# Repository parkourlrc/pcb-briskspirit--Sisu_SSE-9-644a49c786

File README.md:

# Sisu SSE-9

Sisu SSE-9 is an experimental six-layer replacement mainboard for the Nokia
3210 mechanical platform. It keeps the original enclosure, keypad, display,
audio contacts, battery contacts, and bottom connector while replacing the
electronics with an RP2354B application controller and a Telit LE910C1-WWX LTE
module.

Rev B2 has been fabricated and hand assembled. The board is suitable for
development and bring-up, but it is not a drop-in production design.

> [!WARNING]
> Rev B2 has known hardware faults and required post-assembly rework. Read
> [ERRATA.md](ERRATA.md) before ordering, assembling, or powering a board.

| Front | Back |
| --- | --- |
|  |  |

## Key Features

- RP2354B microcontroller with local QSPI flash
- Telit LE910C1-WWX LTE modem and configurable antenna matching networks
- TCA8418 keypad scanner for the original dome-key matrix
- NAU88C22 audio codec with the original earpiece, microphone, speaker, and buzzer interfaces
- BQ25171 dual-chemistry charger support for NiMH and Li-ion development
- LTC2959 charge and current measurement
- RV-8803-C7 real-time clock
- Local symbols, footprints, and 3D models needed by the design
- Service/debug pogo adapter under `subassemblies/debug_pogo_adapter`

## Repository Layout

- `Sisu_SSE-9.kicad_pro`: main KiCad project
- `Sisu_SSE-9.kicad_pcb`: Rev B2 mainboard layout
- `*.kicad_sch`: root and hierarchical schematics
- `lib_10/`: project-local symbols, footprints, and 3D models
- `Sisu_SSE-9_bom_filled.xlsx`: grouped BOM with sourcing and review notes
- `Ordering/`: historical manufacturing archives for fabricated revisions
- `subassemblies/debug_pogo_adapter/`: pogo-to-JST service adapter
- `ERRATA.md`: known Rev B2 faults, rework, and validation limits

## Opening the Project

The current files are saved with KiCad 10.0.5. Clone the repository and open
`Sisu_SSE-9.kicad_pro` from KiCad's project manager. The symbol and footprint
tables use project-relative paths, so no shared user library is required.

```sh
git clone https://github.com/briskspirit/Sisu_SSE-9.git
cd Sisu_SSE-9
```

Older KiCad releases cannot read this project's file format reliably.

## BOM and Assembly

`Sisu_SSE-9.csv`, `Sisu_SSE-9_bom_filled.csv`, and
`Sisu_SSE-9_bom_filled.xlsx` are generated from the current post-assembly Rev
B2 source. The filled workbook retains supplier-review notes, but stock status
is only a historical snapshot and must be checked again before ordering.

RF tuning positions intentionally have no final MPN. Their values are
provisional and depend on the antenna, enclosure, assembly, and calibration.
Mechanical contact footprints such as the display zebra, speaker, motor, and
spring contacts remain visible in the engineering BOM but are excluded from
placement output.

## Manufacturing Archives

The ZIP files under `Ordering/` are immutable records of data sent for previous
fabrication runs. They are useful for comparison, not as the preferred source
for another order. The root KiCad files include post-assembly corrections that
are newer than the Rev B2 archive.

Before fabrication:

1. Read [ERRATA.md](ERRATA.md).
2. Run ERC and DRC with KiCad 10.0.5.
3. Re-export Gerbers, drill files, position files, and the BOM from the root project.
4. Review every fabrication output independently, especially RF footprints, plated holes, and DNP status.

## Current Status

- Rev A established the mechanical and electrical baseline.
- Rev B1 used the u-blox LARA-R6 modem.
- Rev B2 moved to the Telit LE910C1-WWX and is under hardware bring-up.
- Rev C is planned to address the published errata and power-management findings.

Firmware is developed in the sibling `Sisu_DCP-3` project and will be linked
here when its public repository is available.

## Contributing

Issue reports, measurements, footprint corrections, and tested design changes
are welcome. Please identify the board revision, modem variant, battery
chemistry, and the exact test conditions. Hardware changes should include ERC
and DRC results plus a review of generated fabrication data.

## License

Original project material is released under the [Unlicense](COPYING).
Third-party material remains the property of its respective owners; see
[THIRD_PARTY_NOTICES.md](THIRD_PARTY_NOTICES.md).

## Acknowledgements

- KiCad and its library contributors
- Raspberry Pi, Telit, Texas Instruments, Nuvoton, Micro Crystal, and the other component manufacturers whose documentation made this work possible
- The original Nokia 3210 engineering and industrial-design teams

Nokia is a trademark of Nokia Corporation. This is an independent hobby project
and is not affiliated with or endorsed by Nokia, HMD Global, Telit, Raspberry
Pi, or any component manufacturer.

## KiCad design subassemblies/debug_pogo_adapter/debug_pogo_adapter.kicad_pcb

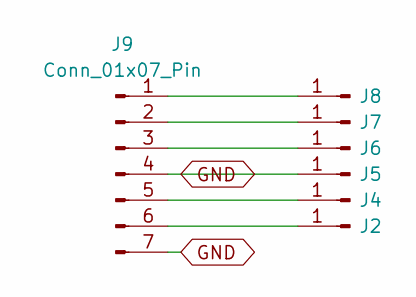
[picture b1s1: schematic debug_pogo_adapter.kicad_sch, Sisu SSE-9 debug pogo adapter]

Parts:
J2, J4, J5, J6, J7, J8: Conn_01x01_Pin; SAMESKY_CPG-01-TH-B
J9: Conn_01x07_Pin; JST_PH_B6B-PH-SM4-TB_1x06-1MP_P2.00mm_Vertical_Shell_GND

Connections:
GND: J5.1 (Pin_1_1), J9.4, J9.7
unnamed: J2.1 (Pin_1_1), J9.6
unnamed: J4.1 (Pin_1_1), J9.5
unnamed: J6.1 (Pin_1_1), J9.3
unnamed: J7.1 (Pin_1_1), J9.2
unnamed: J8.1 (Pin_1_1), J9.1

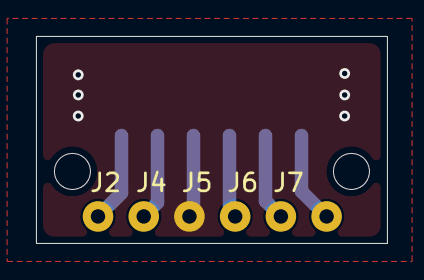
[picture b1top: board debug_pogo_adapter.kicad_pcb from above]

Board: 2 copper layers, 19.5 x 11.5 mm, 7 parts (1 on the bottom side), 6 nets.

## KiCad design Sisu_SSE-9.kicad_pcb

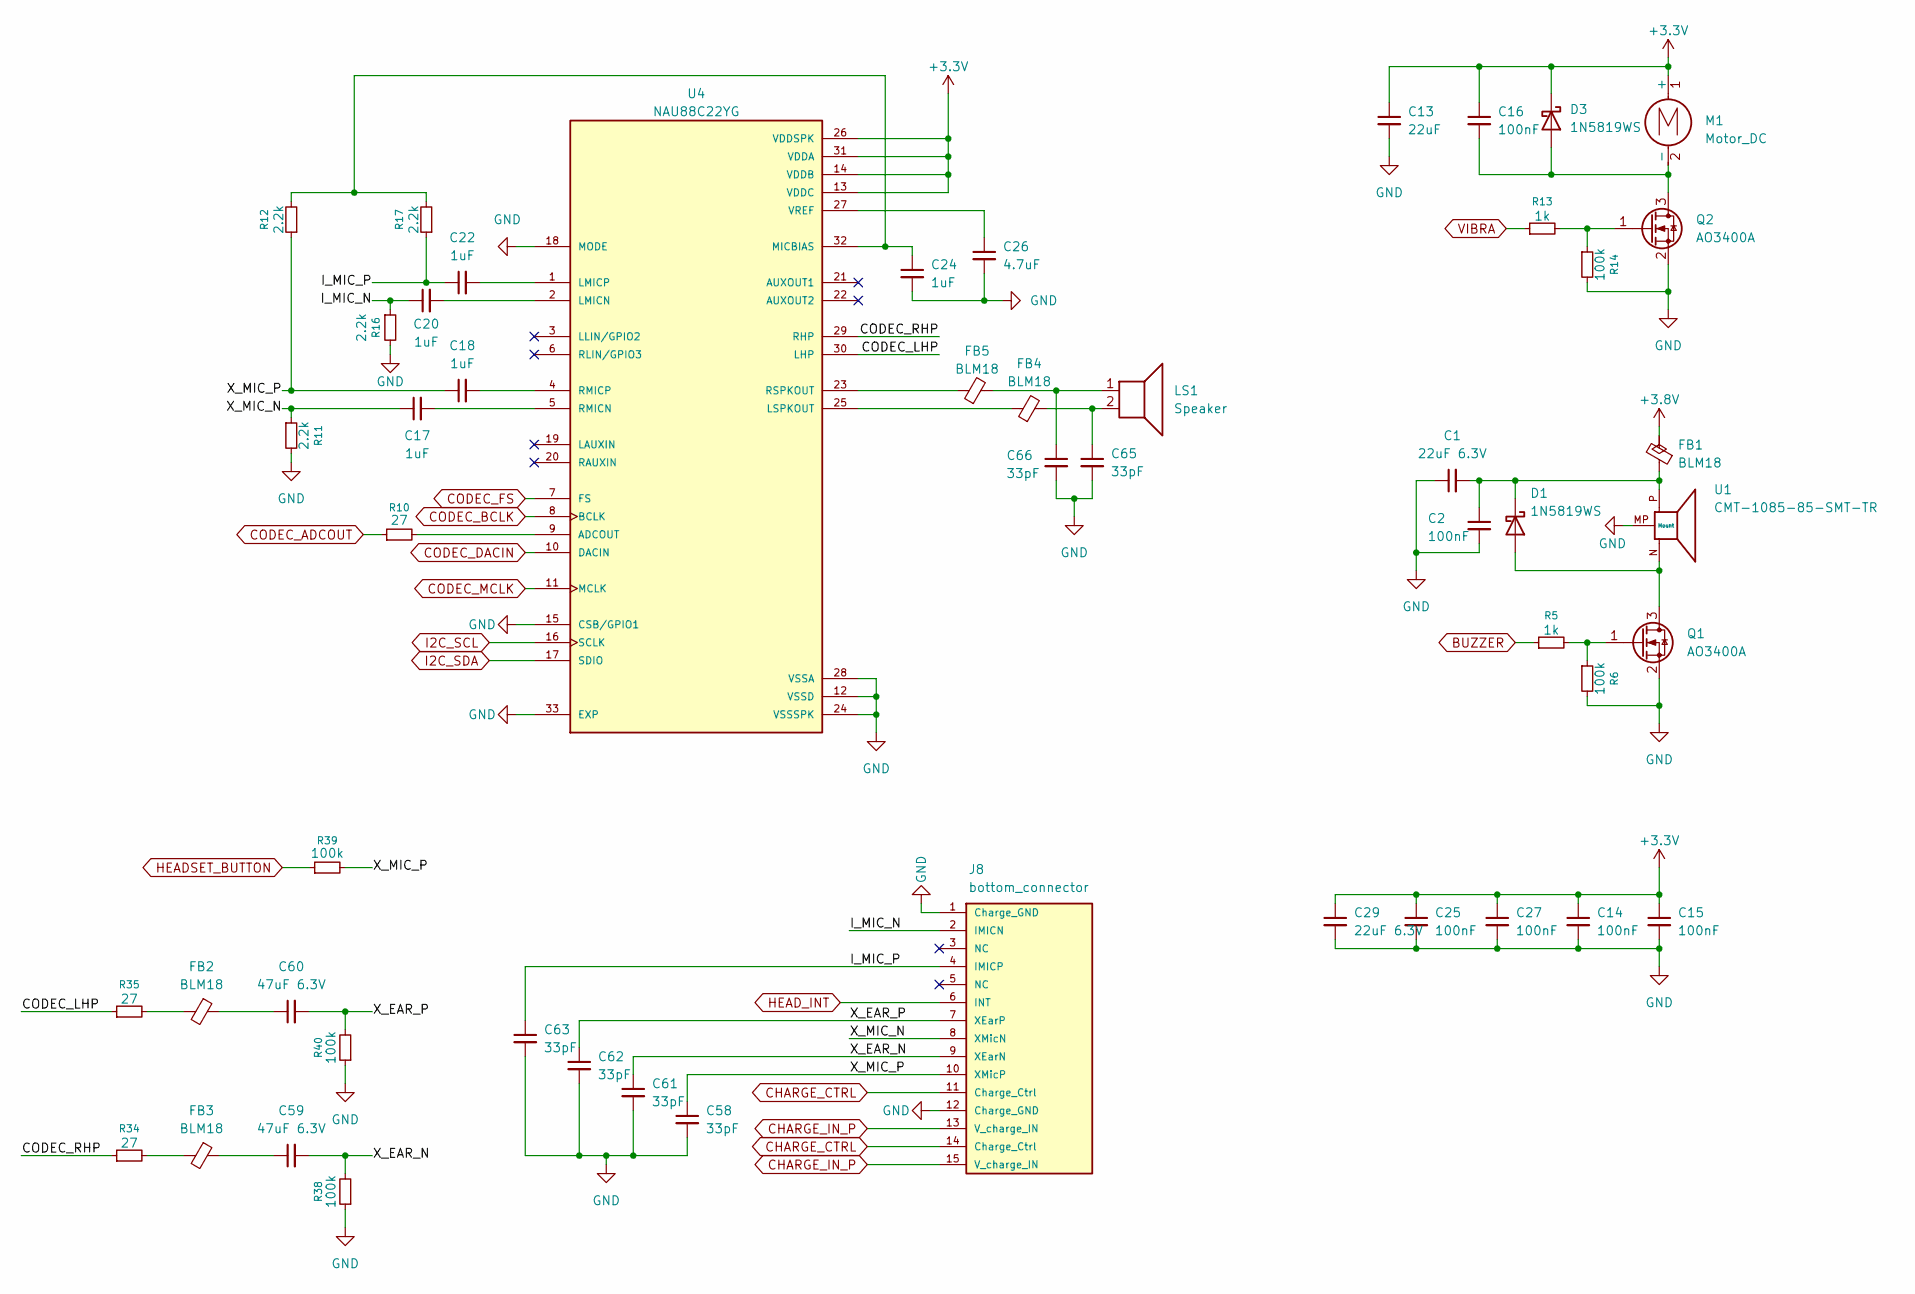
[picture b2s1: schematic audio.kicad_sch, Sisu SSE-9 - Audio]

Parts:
C1, C29: 22uF 6.3V; C_0603_1608Metric
C2, C14, C15, C16, C25, C27: 100nF; C_0402_1005Metric
C13: 22uF; C_0603_1608Metric
C17, C18, C20, C22, C24: 1uF; C_0402_1005Metric
C26: 4.7uF; C_0402_1005Metric
C58, C61, C62, C63, C65, C66: 33pF; C_0402_1005Metric
C59, C60: 47uF 6.3V; C_0805_2012Metric
D1, D3: 1N5819WS; D_SOD-323
FB1, FB2, FB3, FB4, FB5: BLM18; L_0603_1608Metric
J8: bottom_connector; 3210_bottom_conn
LS1: Speaker; Speaker_contact_pads
M1: Motor_DC; 3210_vibra_motor
Q1, Q2: AO3400A; SOT-23
R5, R13: 1k; R_0402_1005Metric
R6, R14, R38, R39, R40: 100k; R_0402_1005Metric
R10, R34, R35: 27; R_0402_1005Metric
R11, R12, R16, R17: 2.2k; R_0402_1005Metric
U1: CMT-1085-85-SMT-TR; MagneticBuzzer_CUI_CMT-1085-85-SMT-TR; PARTREV 1.01
U4: NAU88C22YG; QFN-32-1EP_5x5mm_P0.5mm_EP3.1x3.1mm; PARTREV 3.3

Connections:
+3.3V: C13.1, C14.1, C15.1, C16.1, C25.1, C27.1, C29.1, D3.1 (K), M1.1 (+), U4.13 (VDDC), U4.14 (VDDB), U4.26 (VDDSPK), U4.31 (VDDA); also elsewhere on the board
+3.8V: FB1.2; also elsewhere on the board
/AUDIO/CODEC_LHP: R35.1, U4.30 (LHP)
/AUDIO/CODEC_RHP: R34.1, U4.29 (RHP)
/AUDIO/I_MIC_N: C20.1, J8.2 (IMICN), R16.1
/AUDIO/I_MIC_P: C22.1, C63.1, J8.4 (IMICP), R17.1
/AUDIO/X_EAR_N: C59.2, C61.1, J8.9 (XEarN), R38.2
/AUDIO/X_EAR_P: C60.2, C62.1, J8.7 (XEarP), R40.2
/AUDIO/X_MIC_N: C17.1, J8.8 (XMicN), R11.1
/AUDIO/X_MIC_P: C18.1, C58.1, J8.10 (XMicP), R12.1, R39.2
BUZZER: R5.1; also elsewhere on the board
CHARGE_CTRL: J8.11 (Charge_Ctrl), J8.14 (Charge_Ctrl); also elsewhere on the board
CHARGE_IN_P: J8.13 (V_charge_IN), J8.15 (V_charge_IN); also elsewhere on the board
CODEC_ADCOUT: R10.1; also elsewhere on the board
CODEC_BCLK: U4.8 (BCLK); also elsewhere on the board
CODEC_DACIN: U4.10 (DACIN); also elsewhere on the board
CODEC_FS: U4.7 (FS); also elsewhere on the board
CODEC_MCLK: U4.11 (MCLK); also elsewhere on the board
GND: C1.1, C2.2, C13.2, C14.2, C15.2, C24.2, C25.2, C26.2, C27.2, C29.2, C58.2, C61.2, C62.2, C63.2, C65.2, C66.2, J8.1 (Charge_GND), J8.12 (Charge_GND), Q1.2 (S), Q2.2 (S), R6.2, R11.2, R14.2, R16.2, R38.1, R40.1, U1.MP (Mount_MP), U4.12 (VSSD), U4.15 (CSB/GPIO1), U4.18 (MODE), U4.24 (VSSSPK), U4.28 (VSSA), U4.33 (EXP); also elsewhere on the board
HEADSET_BUTTON: R39.1; also elsewhere on the board
HEAD_INT: J8.6 (INT); also elsewhere on the board
I2C_SCL: U4.16 (SCLK); also elsewhere on the board
I2C_SDA: U4.17 (SDIO); also elsewhere on the board
unnamed: C59.1, FB3.1
unnamed: C60.1, FB2.1
unnamed: C65.1, FB4.2, LS1.2
unnamed: C66.1, FB5.2, LS1.1
unnamed: D1.2 (A), Q1.3 (D), U1.N
unnamed: C1.2, C2.1, D1.1 (K), FB1.1, U1.P
unnamed: C16.2, D3.2 (A), M1.2 (-), Q2.3 (D)
unnamed: FB2.2, R35.2
unnamed: FB3.2, R34.2
unnamed: Q1.1 (G), R5.2, R6.1
unnamed: Q2.1 (G), R13.2, R14.1
unnamed: R10.2, U4.9 (ADCOUT)
unnamed: C20.2, U4.2 (LMICN)
unnamed: C22.2, U4.1 (LMICP)
unnamed: FB4.1, U4.25 (LSPKOUT)
unnamed: C24.1, R12.2, R17.2, U4.32 (MICBIAS)
unnamed: C17.2, U4.5 (RMICN)
unnamed: C18.2, U4.4 (RMICP)
unnamed: FB5.1, U4.23 (RSPKOUT)
unnamed: C26.1, U4.27 (VREF)
VIBRA: R13.1; also elsewhere on the board

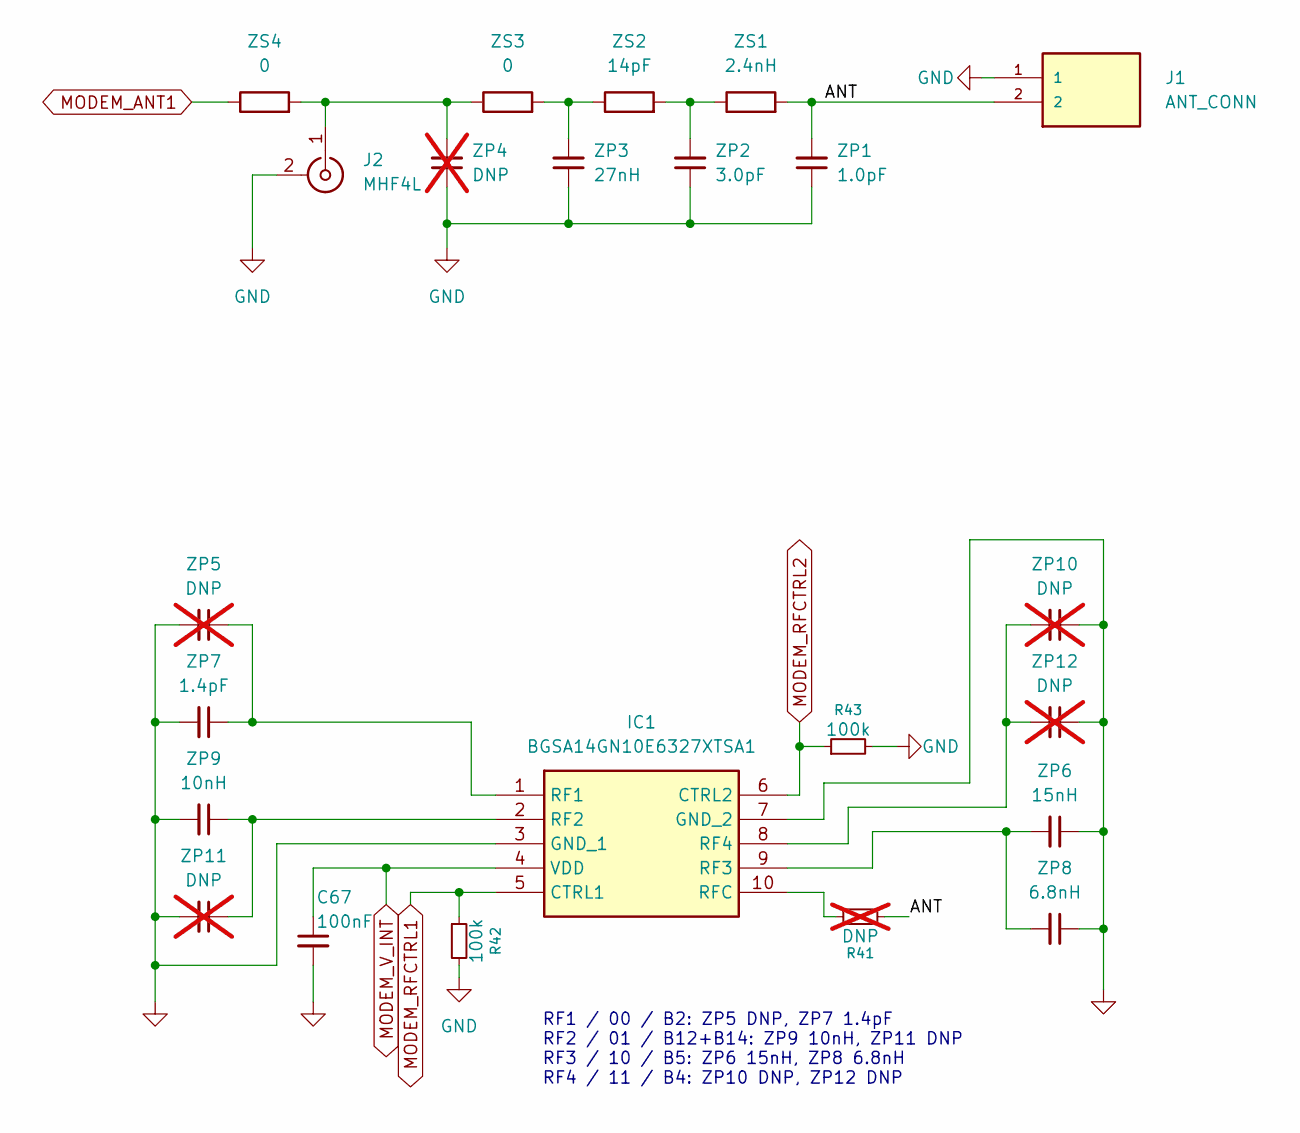
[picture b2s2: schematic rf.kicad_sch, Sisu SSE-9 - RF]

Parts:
C67: 100nF; C_0402_1005Metric
IC1: BGSA14GN10E6327XTSA1; Mouser Part Number 726-BGSA14GN10E6327X
J1: ANT_CONN; XB-BC-12-2P170-08; PARTREV N/A
J2: MHF4L; I-PEX_MHF4L_20579-001E
R41: DNP; R_0402_1005Metric; not fitted
R42, R43: 100k; R_0402_1005Metric
ZP1: 1.0pF; C_0402_1005Metric
ZP2: 3.0pF; C_0402_1005Metric
ZP3: 27nH; C_0402_1005Metric
ZP4, ZP5, ZP10, ZP11, ZP12: DNP; C_0402_1005Metric; not fitted
ZP6: 15nH; C_0402_1005Metric
ZP7: 1.4pF; C_0402_1005Metric
ZP8: 6.8nH; C_0402_1005Metric
ZP9: 10nH; C_0402_1005Metric
ZS1: 2.4nH; C_0402_1005Metric
ZS2: 14pF; C_0402_1005Metric
ZS3, ZS4: 0; C_0402_1005Metric

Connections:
/RF/ANT: J1.2, R41.1, ZP1.2, ZS1.2
GND: C67.2, IC1.3 (GND_1), IC1.7 (GND_2), J1.1, J2.2 (GND), R42.2, R43.2, ZP1.1, ZP2.1, ZP3.1, ZP4.1, ZP5.2, ZP6.1, ZP7.2, ZP8.1, ZP9.2, ZP10.1, ZP11.2, ZP12.1; also elsewhere on the board
MODEM_ANT1: ZS4.1; also elsewhere on the board
MODEM_RFCTRL1: IC1.5 (CTRL1), R42.1; also elsewhere on the board
MODEM_RFCTRL2: IC1.6 (CTRL2), R43.1; also elsewhere on the board
MODEM_V_INT: C67.1, IC1.4 (VDD); also elsewhere on the board
unnamed: IC1.1 (RF1), ZP5.1, ZP7.1
unnamed: IC1.2 (RF2), ZP9.1, ZP11.1
unnamed: IC1.9 (RF3), ZP6.2, ZP8.2
unnamed: IC1.8 (RF4), ZP10.2, ZP12.2
unnamed: IC1.10 (RFC), R41.2
unnamed: J2.1 (RF), ZP4.2, ZS3.1, ZS4.2
unnamed: ZP2.2, ZS1.1, ZS2.2
unnamed: ZP3.2, ZS2.1, ZS3.2

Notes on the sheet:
RF1 / 00 / B2: ZP5 DNP, ZP7 1.4pF RF2 / 01 / B12+B14: ZP9 10nH, ZP11 DNP RF3 / 10 / B5: ZP6 15nH, ZP8 6.8nH RF4 / 11 / B4: ZP10 DNP, ZP12 DNP

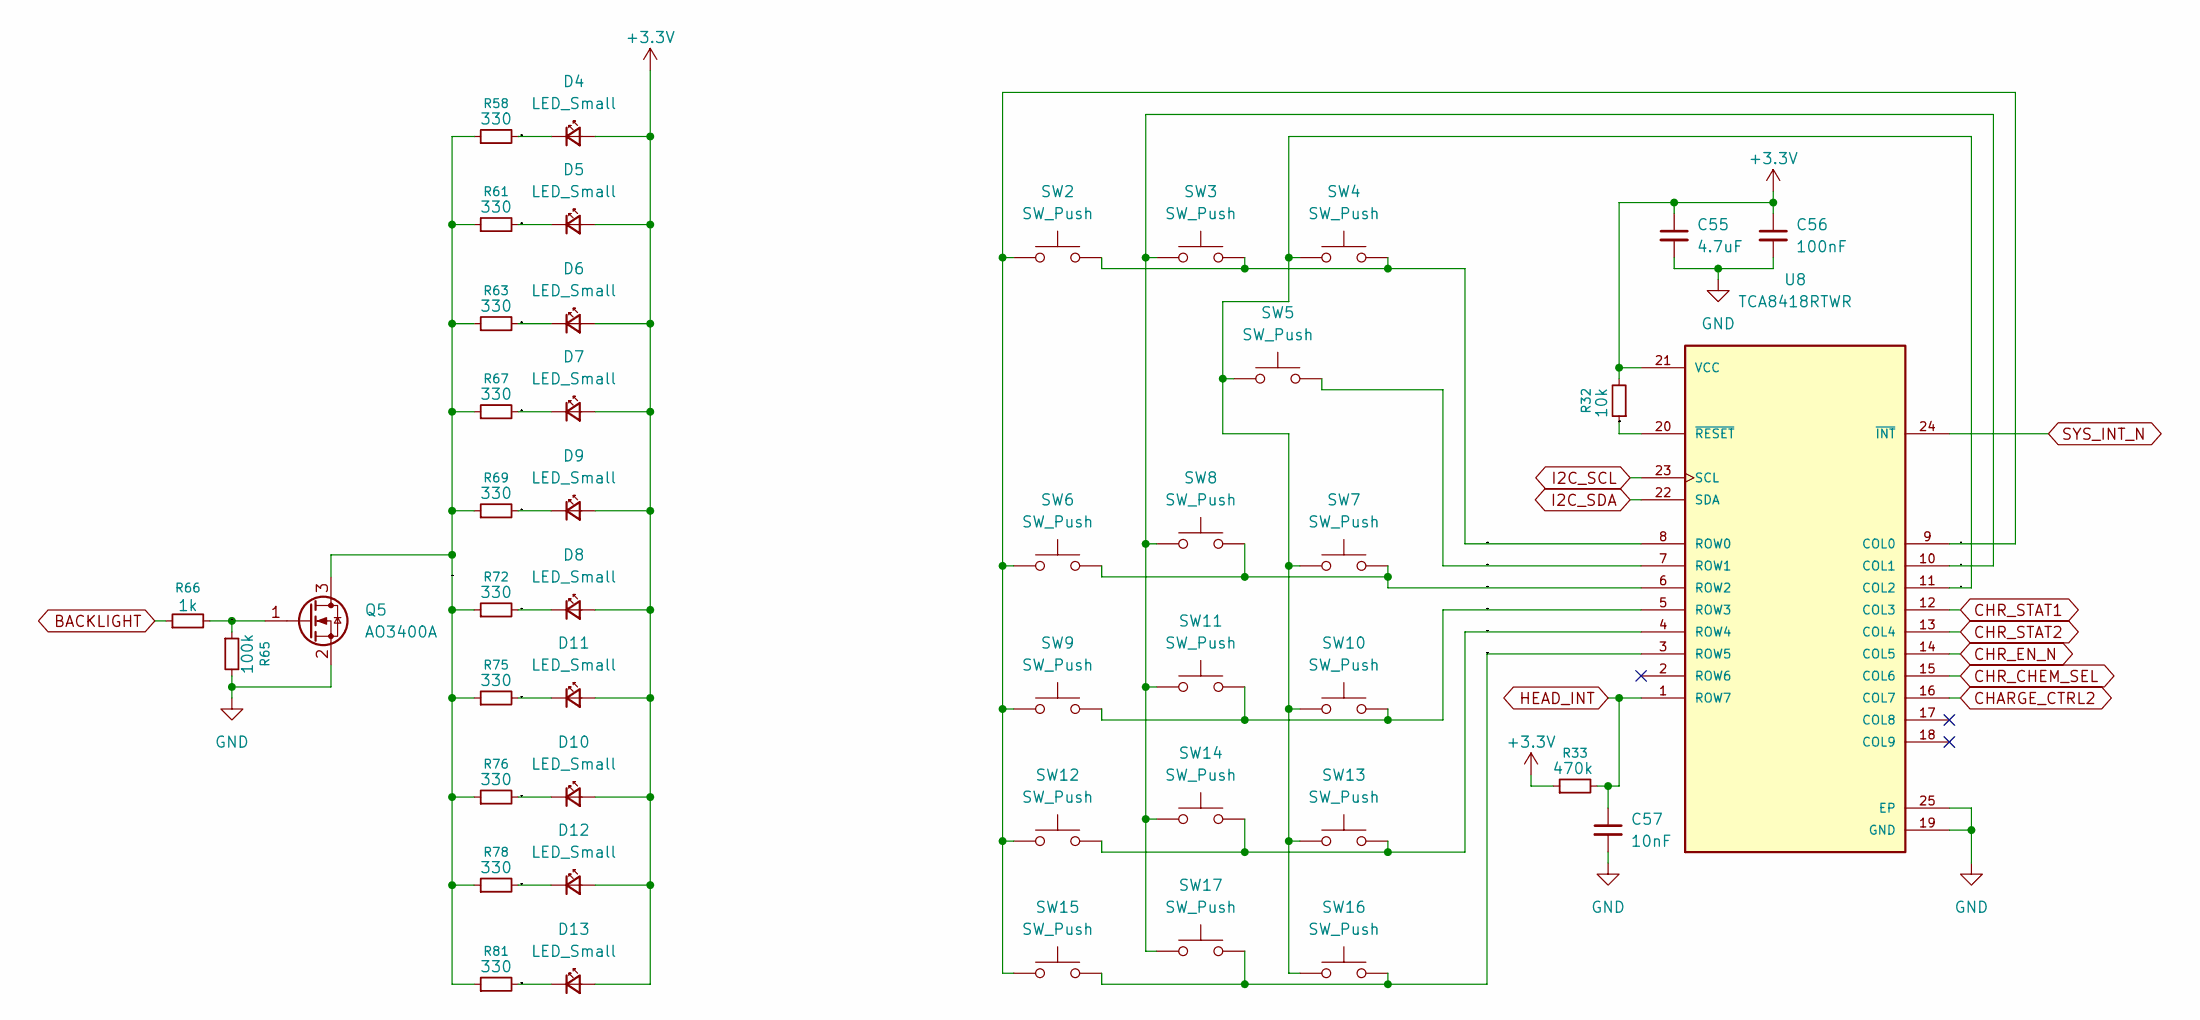
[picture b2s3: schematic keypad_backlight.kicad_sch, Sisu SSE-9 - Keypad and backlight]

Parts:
C55: 4.7uF; C_0402_1005Metric
C56: 100nF; C_0402_1005Metric
C57: 10nF; C_0402_1005Metric
D4, D5, D6, D7, D8, D9, D10, D11, D12, D13: LED_Small; LED_0603_1608Metric
Q5: AO3400A; SOT-23
R32: 10k; R_0402_1005Metric
R33: 470k; R_0402_1005Metric
R58, R61, R63, R67, R69, R72, R75, R76, R78, R81: 330; R_0402_1005Metric
R65: 100k; R_0402_1005Metric
R66: 1k; R_0402_1005Metric
SW2, SW3, SW4, SW5, SW6, SW7, SW8, SW9, SW10, SW11, SW12, SW13, SW14, SW15, SW16, SW17: SW_Push; SW_Dome_Nokia_3210
U8: TCA8418RTWR; QFN50P400X400X80-25N; PARTREV G; DigiKey_Part_Number 296-25223-1-ND

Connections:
+3.3V: C55.1, C56.1, D4.2 (A), D5.2 (A), D6.2 (A), D7.2 (A), D8.2 (A), D9.2 (A), D10.2 (A), D11.2 (A), D12.2 (A), D13.2 (A), R32.2, R33.1, U8.21 (VCC); also elsewhere on the board
/KEYPAD_BACKLIGHT/Net-(D1-K): D4.1 (K), R58.2
/KEYPAD_BACKLIGHT/Net-(D2-K): D5.1 (K), R61.2
/KEYPAD_BACKLIGHT/Net-(D3-K): D6.1 (K), R63.2
/KEYPAD_BACKLIGHT/Net-(D4-K): D7.1 (K), R67.2
/KEYPAD_BACKLIGHT/Net-(D5-K): D9.1 (K), R69.2
/KEYPAD_BACKLIGHT/Net-(D6-K): D8.1 (K), R72.2
/KEYPAD_BACKLIGHT/Net-(D7-K): D11.1 (K), R75.2
/KEYPAD_BACKLIGHT/Net-(D8-K): D10.1 (K), R76.2
/KEYPAD_BACKLIGHT/Net-(D9-K): D12.1 (K), R78.2
/KEYPAD_BACKLIGHT/Net-(D10-K): D13.1 (K), R81.2
/KEYPAD_BACKLIGHT/Net-(Q1-D): Q5.3 (D), R58.1, R61.1, R63.1, R67.1, R69.1, R72.1, R75.1, R76.1, R78.1, R81.1
/KEYPAD_BACKLIGHT/Net-(Q1-G): Q5.1 (G), R65.1, R66.2
/KEYPAD_BACKLIGHT/Net-(U4-COL0): SW2.1, SW6.1, SW9.1, SW12.1, SW15.1, U8.9 (COL0)
/KEYPAD_BACKLIGHT/Net-(U4-COL1): SW3.1, SW8.1, SW11.1, SW14.1, SW17.1, U8.10 (COL1)
/KEYPAD_BACKLIGHT/Net-(U4-COL2): SW4.1, SW5.1, SW7.1, SW10.1, SW13.1, SW16.1, U8.11 (COL2)
/KEYPAD_BACKLIGHT/Net-(U4-ROW0): SW2.2, SW3.2, SW4.2, U8.8 (ROW0)
/KEYPAD_BACKLIGHT/Net-(U4-ROW1): SW5.2, U8.7 (ROW1)
/KEYPAD_BACKLIGHT/Net-(U4-ROW2): SW6.2, SW7.2, SW8.2, U8.6 (ROW2)
/KEYPAD_BACKLIGHT/Net-(U4-ROW3): SW9.2, SW10.2, SW11.2, U8.5 (ROW3)
/KEYPAD_BACKLIGHT/Net-(U4-ROW4): SW12.2, SW13.2, SW14.2, U8.4 (ROW4)
/KEYPAD_BACKLIGHT/Net-(U4-ROW5): SW15.2, SW16.2, SW17.2, U8.3 (ROW5)
/KEYPAD_BACKLIGHT/Net-(U4-~RESET): R32.1, U8.20 (~RESET)
BACKLIGHT: R66.1; also elsewhere on the board
CHARGE_CTRL2: U8.16 (COL7); also elsewhere on the board
CHR_CHEM_SEL: U8.15 (COL6); also elsewhere on the board
CHR_EN_N: U8.14 (COL5); also elsewhere on the board
CHR_STAT1: U8.12 (COL3); also elsewhere on the board
CHR_STAT2: U8.13 (COL4); also elsewhere on the board
GND: C55.2, C56.2, C57.2, Q5.2 (S), R65.2, U8.19 (GND), U8.25 (EP); also elsewhere on the board
HEAD_INT: C57.1, R33.2, U8.1 (ROW7); also elsewhere on the board
I2C_SCL: U8.23 (SCL); also elsewhere on the board
I2C_SDA: U8.22 (SDA); also elsewhere on the board
SYS_INT_N: U8.24 (~INT); also elsewhere on the board

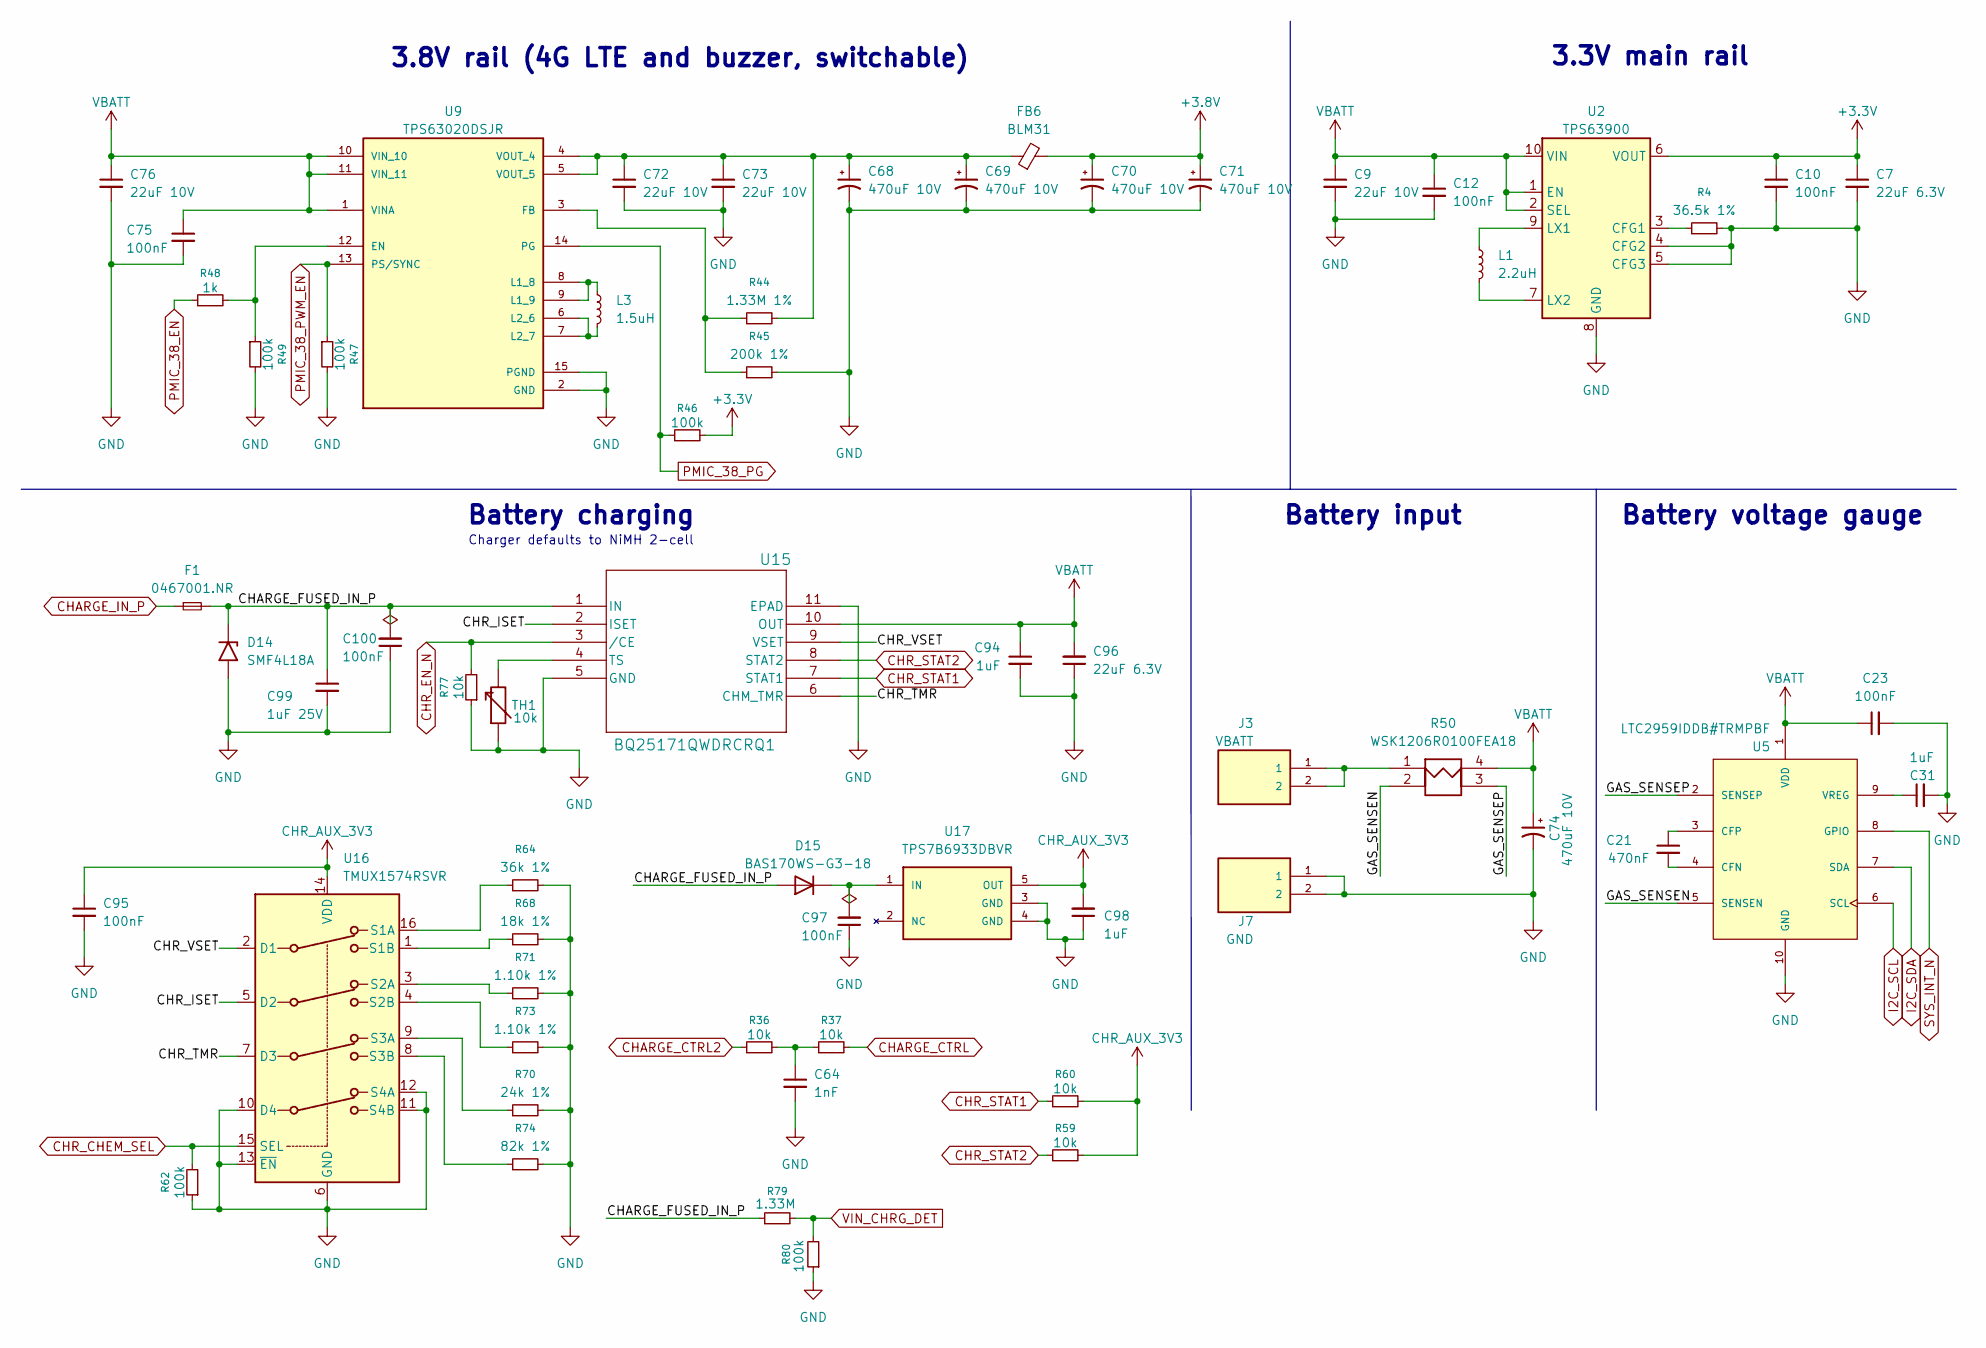
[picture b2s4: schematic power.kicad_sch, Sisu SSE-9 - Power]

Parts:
C7, C96: 22uF 6.3V; C_0603_1608Metric
C9: 22uF 10V; C_0805_2012Metric
C10, C12, C23, C75, C95, C97, C100: 100nF; C_0402_1005Metric
C21: 470nF; C_0402_1005Metric
C31, C94, C98: 1uF; C_0402_1005Metric
C64: 1nF; C_0402_1005Metric
C68, C69, C70, C71, C74: 470uF 10V; CP_EIA-7343-43_AVX-E_Reflow
C72, C73, C76: 22uF 10V; C_1206_3216Metric
C99: 1uF 25V; C_0805_2012Metric
D14: SMF4L18A; D_SOD-123F
D15: BAS170WS-G3-18; D_SOD-323
F1: 0467001.NR; Fuse_0603_1608Metric
FB6: BLM31; BLM31SN500SN1L
J3: VBATT; XB-BC-12-2P170-08; PARTREV N/A
J7: GND; XB-BC-12-2P170-08; PARTREV N/A
L1: 2.2uH; L_1008_2520Metric
L3: 1.5uH; L_Wuerth_MAPI-4030
R4: 36.5k 1%; R_0402_1005Metric
R36, R37, R59, R60, R77: 10k; R_0402_1005Metric
R44: 1.33M 1%; R_0402_1005Metric
R45: 200k 1%; R_0402_1005Metric
R46, R47, R49, R62, R80: 100k; R_0402_1005Metric
R48: 1k; R_0402_1005Metric
R50: WSK1206R0100FEA18
R64: 36k 1%; R_0402_1005Metric
R68: 18k 1%; R_0402_1005Metric
R70: 24k 1%; R_0402_1005Metric
R71, R73: 1.10k 1%; R_0402_1005Metric
R74: 82k 1%; R_0402_1005Metric
R79: 1.33M; R_0402_1005Metric
TH1: 10k; R_0402_1005Metric
U2: TPS63900; WSON-10-1EP_2.5x2.5mm_P0.5mm_EP1.2x2mm_ThermalVias_0.3mm
U5: LTC2959IDDB#TRMPBF; LTC2959IDDB_TRMPBF
U9: TPS63020DSJR; IC_TPS63020DSJR
U15: BQ25171QWDRCRQ1; VSON10_BQ25171_3X3_TEX
U16: TMUX1574RSVR; UQFN-16_1.8x2.6mm_P0.4mm
U17: TPS7B6933DBVR; SOT-23-5_DBV_TPS7B69

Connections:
+3.3V: C7.1, C10.1, R46.2, U2.6 (VOUT); also elsewhere on the board
+3.8V: C70.1, C71.1, FB6.2; also elsewhere on the board
/POWER/CHARGE_FUSED_IN_P: C99.1, C100.2, D14.1 (A1), D15.2 (A), F1.2, R79.1, U15.1 (IN)
/POWER/CHR_ISET: U15.2 (ISET), U16.5 (D2)
/POWER/CHR_TMR: U15.6 (CHM_TMR), U16.7 (D3)
/POWER/CHR_VSET: U15.9 (VSET), U16.2 (D1)
/POWER/GAS_SENSEN: R50.2, U5.5 (SENSEN)
/POWER/GAS_SENSEP: R50.3, U5.2 (SENSEP)
CHARGE_CTRL: R37.2; also elsewhere on the board
CHARGE_CTRL2: R36.1; also elsewhere on the board
CHARGE_IN_P: F1.1; also elsewhere on the board
CHR_AUX_3V3: C95.1, C98.2, R59.2, R60.2, U16.14 (VDD), U17.5 (OUT)
CHR_CHEM_SEL: R62.2, U16.15 (SEL); also elsewhere on the board
CHR_EN_N: R77.2, U15.3 (/CE); also elsewhere on the board
CHR_STAT1: R60.1, U15.7 (STAT1); also elsewhere on the board
CHR_STAT2: R59.1, U15.8 (STAT2); also elsewhere on the board
GND: C7.2, C9.2, C10.2, C12.2, C23.2, C31.2, C64.2, C68.2, C69.2, C70.2, C71.2, C72.2, C73.2, C74.2, C75.2, C76.2, C94.2, C95.2, C96.1, C97.1, C98.1, C99.2, C100.1, D14.2 (A2), J7.1, J7.2, R4.2, R45.2, R47.2, R49.2, R62.1, R64.2, R68.2, R70.2, R71.2, R73.2, R74.2, R77.1, R80.1, TH1.1, U2.4 (CFG2), U2.5 (CFG3), U2.8 (GND), U2.11 (GND), U5.10 (GND), U9.2 (GND), U9.15 (PGND), U15.5 (GND), U15.11 (EPAD), U16.6 (GND), U16.10 (D4), U16.11 (S4B), U16.12 (S4A), U16.13 (~EN), U17.3 (GND), U17.4 (GND); also elsewhere on the board
I2C_SCL: U5.6 (SCL); also elsewhere on the board
I2C_SDA: U5.7 (SDA); also elsewhere on the board
unnamed: C64.1, R36.2, R37.1
unnamed: C97.2, D15.1 (K), U17.1 (IN)
unnamed: J3.1, J3.2, R50.1
unnamed: R4.1, U2.3 (CFG1)
unnamed: L1.1, U2.9 (LX1)
unnamed: L1.2, U2.7 (LX2)
unnamed: C21.2, U5.4 (CFN)
unnamed: C21.1, U5.3 (CFP)
unnamed: C31.1, U5.9 (VREG)
unnamed: R48.2, R49.1, U9.12 (EN)
unnamed: R44.1, R45.1, U9.3 (FB)
unnamed: L3.1, U9.8 (L1_8), U9.9 (L1_9)
unnamed: L3.2, U9.6 (L2_6), U9.7 (L2_7)
unnamed: C68.1, C69.1, C72.1, C73.1, FB6.1, R44.2, U9.4 (VOUT_4), U9.5 (VOUT_5)
unnamed: TH1.2, U15.4 (TS)
unnamed: R64.1, U16.16 (S1A)
unnamed: R68.1, U16.1 (S1B)
unnamed: R71.1, U16.3 (S2A)
unnamed: R73.1, U16.4 (S2B)
unnamed: R70.1, U16.9 (S3A)
unnamed: R74.1, U16.8 (S3B)
PMIC_38_EN: R48.1; also elsewhere on the board
PMIC_38_PG: R46.1, U9.14 (PG); also elsewhere on the board
PMIC_38_PWM_EN: R47.1, U9.13 (PS/SYNC); also elsewhere on the board
SYS_INT_N: U5.8 (GPIO); also elsewhere on the board
VBATT: C9.1, C12.1, C23.1, C74.1, C75.1, C76.1, C94.1, C96.2, R50.4, U2.1 (EN), U2.2 (SEL), U2.10 (VIN), U5.1 (VDD), U9.1 (VINA), U9.10 (VIN_10), U9.11 (VIN_11), U15.10 (OUT)
VIN_CHRG_DET: R79.2, R80.2; also elsewhere on the board

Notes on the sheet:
3.3V main rail
Charger defaults to NiMH 2-cell
Battery voltage gauge
3.8V rail (4G LTE and buzzer, switchable)
Battery charging
Battery input
